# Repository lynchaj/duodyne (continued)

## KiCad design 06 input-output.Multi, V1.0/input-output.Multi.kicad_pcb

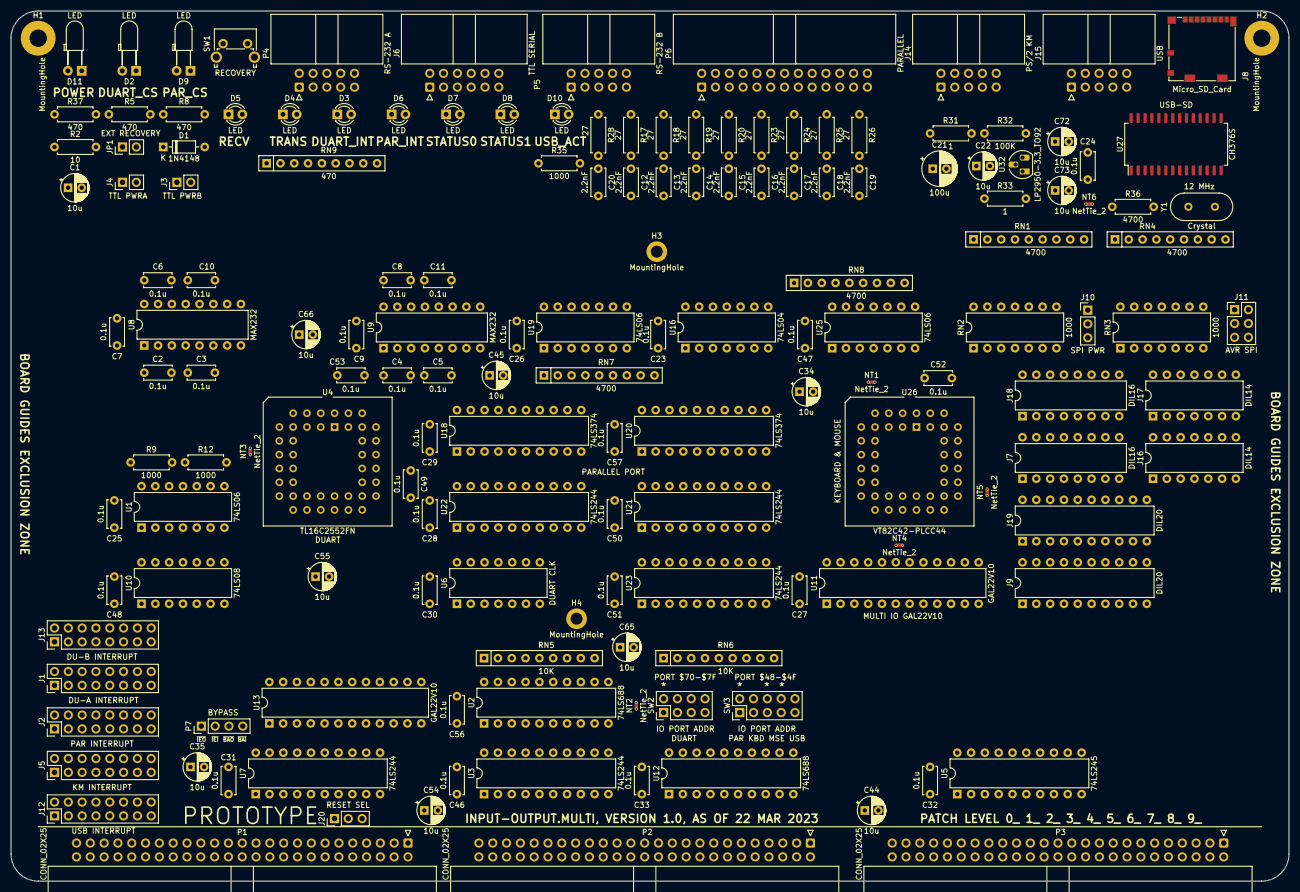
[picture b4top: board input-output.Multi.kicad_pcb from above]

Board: 2 copper layers, 235.0 x 160.0 mm, 159 parts (0 on the bottom side), 229 nets, no tracks yet.

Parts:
C1, C22, C34, C35, C44, C45, C54, C55, C65, C66, C72, C73: 10u; CP_Radial_D5.0mm_P2.50mm
C2, C3, C4, C5, C6, C7, C8, C9, C10, C11, C23, C24, C25, C26, C27, C28, C29, C30, C31, C32, C33, C46, C47, C48, C49, C50, C51, C52, C53, C56, C57: 0.1u; C_Disc_D5.0mm_W2.5mm_P5.00mm
C12, C13, C14, C15, C16, C17, C18, C19, C20: 2.2nF; C_Disc_D5.0mm_W2.5mm_P5.00mm
C21: 100u; CP_Radial_D6.3mm_P2.50mm
D1: 1N4148; D_DO-35_SOD27_P7.62mm_Horizontal
D2, D9, D11: LED; LED_D3.0mm_Horizontal_O3.81mm_Z2.0mm
D3, D4, D5, D6, D7, D8, D10: LED; LED_D3.0mm
H1, H2: MountingHole; MountingHole_3.2mm_M3_Pad
H3, H4: MountingHole; MountingHole_2.2mm_M2_DIN965_Pad
J1: DU-A INTERRUPT; PinHeader_2x08_P2.54mm_Vertical
J2: PAR INTERRUPT; PinHeader_2x08_P2.54mm_Vertical
J3: TTL PWRB; PinHeader_1x02_P2.54mm_Vertical
J4: TTL PWRA; PinHeader_1x02_P2.54mm_Vertical
J5: KM INTERRUPT; PinHeader_2x08_P2.54mm_Vertical
J6: TTL SERIAL; IDC-Header_2x06_P2.54mm_Horizontal
J7, J18: DIL16; DIP-16_W7.62mm
J8: Micro_SD_Card; microSD_HC_Molex_104031-0811
J9, J19: DIL20; DIP-20_W7.62mm
J10: SPI PWR; PinHeader_1x03_P2.54mm_Vertical
J11: AVR SPI; PinHeader_2x03_P2.54mm_Vertical
J12: USB INTERRUPT; PinHeader_2x08_P2.54mm_Vertical
J13: DU-B INTERRUPT; PinHeader_2x08_P2.54mm_Vertical
J14: PS/2 KM; IDC-Header_2x05_P2.54mm_Horizontal
J15: USB; IDC-Header_2x05_P2.54mm_Horizontal
J16, J17: DIL14; DIP-14_W7.62mm
J20: RESET SEL; PinHeader_1x03_P2.54mm_Vertical
JP1: EXT RECOVERY; PinHeader_1x02_P2.54mm_Vertical
NT1, NT2, NT3, NT4, NT5, NT6: NetTie_2; NetTie-2_THT_Pad0.3mm
P1, P2, P3: CONN_02X25; IDC-Header_2x25_P2.54mm_Horizontal
P4: RS-232 A; IDC-Header_2x05_P2.54mm_Horizontal
P5: RS-232 B; IDC-Header_2x05_P2.54mm_Horizontal
P6: PARALLEL; IDC-Header_2x13_P2.54mm_Horizontal
P7: BYPASS; PinHeader_1x04_P2.54mm_Vertical
R2: 10; R_Axial_DIN0207_L6.3mm_D2.5mm_P7.62mm_Horizontal
R5, R8, R37: 470; R_Axial_DIN0207_L6.3mm_D2.5mm_P7.62mm_Horizontal
R9, R12, R35: 1000; R_Axial_DIN0207_L6.3mm_D2.5mm_P7.62mm_Horizontal
R17, R18, R19, R20, R23, R24, R25, R26, R28: 27; R_Axial_DIN0207_L6.3mm_D2.5mm_P7.62mm_Horizontal
R31, R33: 1; R_Axial_DIN0207_L6.3mm_D2.5mm_P7.62mm_Horizontal
R32: 100K; R_Axial_DIN0207_L6.3mm_D2.5mm_P7.62mm_Horizontal
R36: 4700; R_Axial_DIN0207_L6.3mm_D2.5mm_P7.62mm_Horizontal
RN1, RN4, RN7, RN8: 4700; R_Array_SIP9
RN2, RN3: 1000; DIP-14_W7.62mm
RN5, RN6: 10K; R_Array_SIP9
RN9: 470; R_Array_SIP9
SW1: RECOVERY; SW_Tactile_SPST_Angled_PTS645Vx58-2LFS
SW2: IO PORT ADDR; PinHeader_2x04_P2.54mm_Vertical
SW3: IO PORT ADDR; PinHeader_2x05_P2.54mm_Vertical
U1, U19, U25: 74LS06; DIP-14_W7.62mm
U2, U12: 74LS688; DIP-20_W7.62mm
U3, U7, U21, U22, U23: 74LS244; DIP-20_W7.62mm
U4: TL16C2552FN; PLCC-44_THT-Socket
U5: 74LS245; DIP-20_W7.62mm
U6: DUART CLK; DIP-14_W7.62mm
U8, U9: MAX232; DIP-16_W7.62mm
U10: 74LS08; DIP-14_W7.62mm
U11, U13: GAL22V10; DIP-24_W7.62mm
U16: 74LS04; DIP-14_W7.62mm
U18, U20: 74LS374; DIP-20_W7.62mm
U26: VT82C42-PLCC44; PLCC-44_THT-Socket
U27: CH376S; SOIC-28W_7.5x18.7mm_P1.27mm
U32: LP2950-3.3_TO92; TO-92_HandSolder
Y1: Crystal; Crystal_HC49-4H_Vertical

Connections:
470A: D2.2 (A), RN9.2 (R1)
470B: D9.2 (A), RN9.3 (R2)
470C: D5.2 (A), RN9.4 (R3)
470D: D4.2 (A), RN9.5 (R4)
470E: D3.2 (A), RN9.6 (R5)
470F: D6.2 (A), RN9.7 (R6)
470G: D7.2 (A), RN9.8 (R7)
470H: D8.2 (A), RN9.9 (R8)
+12V: P2.19, P2.20
-12V: P2.37, P2.38
/DUART/GND_UART: NT3.1, U4.12 (GND)
/DUART/INTA: R12.1, U1.5, U4.34 (INTA)
/DUART/INTB: R9.1, U1.3, U4.17 (INTB)
/DUART/RXA: P4.3, U8.8 (R2IN)
/DUART/RXB: P5.3, U9.8 (R2IN)
/DUART/TTL_RXA: J6.7, U4.39 (RXA), U8.9 (R2OUT), U10.4
/DUART/TTL_RXB: J6.8, U4.25 (RXB), U9.9 (R2OUT), U10.5
/DUART/TTL_TXA: J6.9, U4.38 (TXA), U8.10 (T2IN), U10.1
/DUART/TTL_TXB: J6.10, U4.26 (TXB), U9.10 (T2IN), U10.2
/DUART/TXA: P4.5, U8.7 (T2OUT)
/DUART/TXB: P5.5, U9.7 (T2OUT)
/DUART/~CTSA: P4.6, U8.13 (R1IN)
/DUART/~CTSB: P5.6, U9.13 (R1IN)
/DUART/~DTRA: P4.7, R5.1
/DUART/~DTRB: P5.7, R8.1
/DUART/~INTA: J1.1, J1.3, J1.5, J1.7, J1.9, J1.11, J1.13, J1.15, U1.6, U10.9
/DUART/~INTB: J13.1, J13.3, J13.5, J13.7, J13.9, J13.11, J13.13, J13.15, U1.4, U10.10
/DUART/~RTSA: P4.4, U8.14 (T1OUT)
/DUART/~RTSB: P5.4, U9.14 (T1OUT)
/DUART/~TTL_CTSA: J6.11, U4.40 (~CTSA), U8.12 (R1OUT)
/DUART/~TTL_CTSB: J6.12, U4.28 (~CTSB), U9.12 (R1OUT)
/DUART/~TTL_RIA: C1.1, D1.2 (A), R2.2, RN5.9 (R8), U4.43 (~RIA)
/DUART/~TTL_RTSA: J6.3, U4.36 (~RTSA), U8.11 (T1IN)
/DUART/~TTL_RTSB: J6.4, U4.23 (~RTSB), U9.11 (T1IN)
/USB-SD/RST: R36.1, RN3.9 (R6.2), U27.2 (RSTI)
/USB-SD/SDCK: J8.5 (CLK), J11.3, U27.26 (SD_CK)
/USB-SD/SDCS: J8.2 (DAT3/CD), J11.5, RN4.6 (R5), U27.23 (SD_CS)
/USB-SD/SDDI: J8.3 (CMD), J11.1, U27.25 (SD_DO)
/USB-SD/SDDO: J8.7 (DAT0), J11.4, RN4.7 (R6), U27.7 (SD_DI)
/USB-SD/UD+: J15.5, J15.6, U27.10 (UD+)
/USB-SD/UD-: J15.3, J15.4, U27.11 (UD-)
/USB-SD/VBUS: C21.1, J15.1, J15.2, R31.2
/USB-SD/VDD2: C24.1, NT6.1, U27.28 (VCC)
/USB-SD/VDD3: C22.1, C23.1, J8.4 (VDD), R33.2
/USB-SD/~INT-USB: RN4.8 (R7), U16.1, U27.1 (~INT)
/kbdmse/KBDCLK: J14.1, RN8.3 (R2), U25.4, U26.2 (T0)
/kbdmse/KBDDAT: J14.9, RN8.5 (R4), U25.2, U26.30 (P10)
/kbdmse/MSECLK: J14.2, RN8.2 (R1), U25.8, U26.43 (T1)
/kbdmse/MSEDAT: J14.10, RN8.4 (R3), U25.6, U26.31 (P11)
/kbdmse/PROG: RN8.6 (R5), U26.28 (PROG)
/kbdmse/~INT_KM: J5.1, J5.3, J5.5, J5.7, J5.9, J5.11, J5.13, J5.15, U25.12
/parallel/BUSY: RN7.6 (R5), U19.2, U21.17 (I3b)
/parallel/ERROR: P6.4, U21.8 (I3a)
/parallel/P-RESET: P6.6, RN7.4 (R3), U19.10, U23.6 (I2a)
/parallel/PAPEROUT: P6.23, U21.13 (I1b)
/parallel/PD0: C12.1, P6.3, R17.1, U22.2 (I0a)
/parallel/PD1: C13.1, P6.5, R18.1, U22.4 (I1a)
/parallel/PD2: C14.1, P6.7, R19.1, U22.6 (I2a)
/parallel/PD3: C15.1, P6.9, R20.1, U22.8 (I3a)
/parallel/PD4: C16.1, P6.11, R23.1, U22.11 (I0b)
/parallel/PD5: C17.1, P6.13, R24.1, U22.13 (I1b)
/parallel/PD6: C18.1, P6.15, R25.1, U22.15 (I2b)
/parallel/PD7: C19.1, P6.17, R26.1, U22.17 (I3b)
/parallel/SELECT: P6.25, U21.11 (I0b)
/parallel/STATUS0: P6.26, U1.11, U20.16 (O6), U23.15 (I2b)
/parallel/STATUS1: U1.13, U20.19 (O7), U23.17 (I3b)
/parallel/~BUSY: P6.21, U19.1
/parallel/~INT_PAR: J2.1, J2.3, J2.5, J2.7, J2.9, J2.11, J2.13, J2.15, U19.12
/parallel/~LINEFEED: P6.2, RN7.3 (R2), U16.11, U19.8
/parallel/~PDENBL: U18.1 (OE), U20.15 (O5), U23.13 (I1b)
/parallel/~SEL: P6.8, RN7.5 (R4), U16.13, U19.4
/parallel/~STROBE: C20.1, P6.1, R28.1, RN7.2 (R1), U16.9
A0: P2.35, U3.2 (I0a)
A1: P2.33, U3.4 (I1a)
A2: P2.31, U3.6 (I2a)
A3: P2.29, U3.8 (I3a)
A4: P2.27, U3.11 (I0b)
A5: P2.25, U3.13 (I1b)
A6: P2.23, U3.15 (I2b)
A7: P2.21, U3.17 (I3b)
ACK: P6.19, U11.10 (I9), U21.15 (I2b)
CLK_DUART: U4.11 (XTAL1), U6.8, U6.11, U26.4 (X2)
D0: P3.33, U5.2 (A0)
D1: P3.31, U5.3 (A1)
D2: P3.29, U5.4 (A2)
D3: P3.27, U5.5 (A3)
D4: P3.25, U5.6 (A4)
D5: P3.23, U5.7 (A5)
D6: P3.21, U5.8 (A6)
D7: P3.19, U5.9 (A7)
GND: C1.2, C7.2, C9.2, C10.2, C11.2, C12.2, C13.2, C14.2, C15.2, C16.2, C17.2, C18.2, C19.2, C20.2, C21.2, C22.2, C23.2, C24.2, C25.2, C26.2, C27.2, C28.2, C29.2, C30.2, C31.2, C32.2, C33.2, C34.2, C35.2, C44.2, C45.2, C46.2, C47.2, C48.2, C49.2, C50.2, C51.2, C52.2, C53.2, C54.2, C55.2, C56.2, C57.2, C65.2, C66.2, C72.2, C73.2, D11.1 (K), H1.1, H2.1, J6.1, J6.2, J8.6 (VSS), J8.9 (SHIELD), J11.6, J14.5, J14.6, J15.7, J15.8, JP1.1 (A), NT2.1, NT3.2, NT4.1, P1.49, P1.50, P2.49, P2.50, P3.49, P3.50, P4.9, P5.9, P6.10, P6.12, P6.14, P6.16, P6.18, P6.20, P6.22, P6.24, R9.2, R12.2, R36.2, SW1.1, U1.7 (GND), U2.10 (GND), U3.10 (GND), U4.22 (GND), U5.10 (GND), U6.4, U6.7, U7.10 (GND), U8.15 (GND), U9.15 (GND), U10.7 (GND), U11.12 (GND), U12.10 (GND), U13.12 (GND), U16.7 (GND), U18.10 (GND), U19.7 (GND), U20.10 (GND), U21.10 (GND), U22.10 (GND), U23.10 (GND), U25.7 (GND), U27.12 (GND), U32.2 (GND)
INT_KM: U11.14 (O9), U25.13
INT_PAR: U1.9, U11.15 (O8), U19.13
unnamed: C2.1, U8.1 (C1+)
unnamed: C2.2, U8.3 (C1-)
unnamed: C3.1, U8.4 (C2+)
unnamed: C3.2, U8.5 (C2-)
unnamed: C4.1, U9.1 (C1+)
unnamed: C4.2, U9.3 (C1-)
unnamed: C5.1, U9.4 (C2+)
unnamed: C5.2, U9.5 (C2-)
unnamed: C6.2, U8.2 (VS+)
unnamed: C8.2, U9.2 (VS+)
unnamed: C10.1, U8.6 (VS-)
unnamed: C11.1, U9.6 (VS-)
unnamed: D2.1 (K), U7.16 (O1a)
unnamed: D3.1 (K), U10.8
unnamed: D4.1 (K), U10.3
unnamed: D5.1 (K), U10.6
unnamed: D6.1 (K), U1.8
unnamed: D7.1 (K), U1.10
unnamed: D8.1 (K), U1.12
unnamed: D9.1 (K), U10.11
unnamed: D10.1 (K), R35.1
unnamed: D11.2 (A), R37.1
unnamed: J3.2, J6.6
unnamed: J4.2, J6.5
unnamed: J8.1 (DAT2), J8.8 (DAT1), R32.2
unnamed: J10.2, J11.2
unnamed: J12.1, J12.3, J12.5, J12.7, J12.9, J12.11, J12.13, J12.15, U25.10
unnamed: J20.2, U7.2 (I0a)
unnamed: JP1.2 (B), R2.1, SW1.2
unnamed: R17.2, U18.2 (O0)
unnamed: R18.2, U18.5 (O1)
unnamed: R19.2, U18.6 (O2)
unnamed: R20.2, U18.9 (O3)
unnamed: R23.2, U18.12 (O4)
unnamed: R24.2, U18.15 (O5)
unnamed: R25.2, U18.16 (O6)
unnamed: R26.2, U18.19 (O7)
unnamed: R28.2, U19.6
unnamed: R35.2, U27.24 (~ACT)
unnamed: RN1.2 (R1), RN3.14 (R1.2), U27.22 (D7)
unnamed: RN1.3 (R2), RN2.14 (R1.2), U27.21 (D6)
unnamed: RN1.4 (R3), RN2.13 (R2.2), U27.20 (D5)
unnamed: RN1.5 (R4), RN2.12 (R3.2), U27.19 (D4)
unnamed: RN1.6 (R5), RN2.11 (R4.2), U27.18 (D3)
unnamed: RN1.7 (R6), RN2.10 (R5.2), U27.17 (D2)
unnamed: RN1.8 (R7), RN2.9 (R6.2), U27.16 (D1)
unnamed: RN1.9 (R8), RN2.8 (R7.2), U27.15 (D0)
unnamed: RN3.10 (R5.2), RN4.5 (R4), U27.27 (~PCS)
unnamed: RN3.11 (R4.2), RN4.4 (R3), U27.3 (~WR)
unnamed: RN3.12 (R3.2), RN4.3 (R2), U27.4 (~RD)
unnamed: RN3.13 (R2.2), RN4.2 (R1), U27.8 (A0)
unnamed: RN5.2 (R1), SW2.1, U2.18 (R7)
unnamed: RN5.3 (R2), SW2.3, U2.16 (R6)
unnamed: RN5.4 (R3), SW2.5, U2.14 (R5)
unnamed: RN5.5 (R4), SW2.7, U2.12 (R4)
unnamed: RN5.6 (R5), U2.3 (R0), U2.4 (P1), U2.5 (R1), U2.6 (P2), U2.7 (R2), U2.8 (P3), U2.9 (R3)
unnamed: RN6.2 (R1), SW3.1, U12.18 (R7)
unnamed: RN6.3 (R2), SW3.3, U12.16 (R6)
unnamed: RN6.4 (R3), SW3.5, U12.14 (R5)
unnamed: RN6.5 (R4), SW3.7, U12.12 (R4)
unnamed: RN6.6 (R5), SW3.9, U12.9 (R3)
unnamed: RN6.7 (R6), U12.3 (R0), U12.4 (P1), U12.5 (R1), U12.6 (P2), U12.7 (R2)
unnamed: U16.2, U25.11
unnamed: U16.5, U20.6 (O2)
unnamed: U16.6, U19.11
unnamed: U16.8, U23.2 (I0a)
unnamed: U16.10, U23.4 (I1a)
unnamed: U16.12, U23.8 (I3a)
unnamed: U19.3, U20.9 (O3)
unnamed: U19.5, U20.2 (O0)
unnamed: U19.9, U20.5 (O1)
unnamed: U25.1, U26.42 (P27/DAK)
unnamed: U25.3, U26.41 (P26/DRQ)
unnamed: U25.5, U26.26 (P22)
unnamed: U25.9, U26.27 (P23)
unnamed: U27.13 (XI), Y1.1
unnamed: U27.14 (XO), Y1.2
ONE: NT1.2, U26.6 (SS)
P24-OB: U11.11 (I10), U26.39 (P24/OB)
P25-BF: U11.13 (I11), U26.40 (P25/BF)
PARINT: U11.9 (I8), U20.12 (O4), U23.11 (I0b)
VCC: C6.1, C7.1, C8.1, C9.1, C25.1, C26.1, C27.1, C28.1, C29.1, C30.1, C31.1, C32.1, C33.1, C34.1, C35.1, C44.1, C45.1, C46.1, C47.1, C48.1, C49.1, C50.1, C51.1, C52.1, C53.1, C54.1, C55.1, C56.1, C57.1, C65.1, C66.1, C72.1, D1.1 (K), J3.1, J4.1, J10.3, J14.3, J14.4, NT1.1, NT5.2, P1.1, P1.2, P2.1, P2.2, P3.1, P3.2, R5.2, R8.2, R31.1, R37.2, RN5.1 (common), RN6.1 (common), RN7.1 (common), RN8.1 (common), RN9.1 (common), U1.14 (VCC), U2.20 (VCC), U3.20 (VCC), U4.33 (VCC), U4.44 (VCC), U5.20 (VCC), U6.1, U6.14, U7.20 (VCC), U8.16 (VCC), U9.16 (VCC), U10.14 (VCC), U11.24 (VCC), U12.20 (VCC), U13.24 (VCC), U16.14 (VCC), U18.20 (VCC), U19.14 (VCC), U20.20 (VCC), U21.20 (VCC), U22.20 (VCC), U23.20 (VCC), U25.14 (VCC), U26.44 (VCC), U32.3 (VI)
VDD: NT5.1, U26.29 (VDD)
VDD1: C73.1, D10.2 (A), J10.1, NT6.2, R32.1, R33.1, RN1.1 (common), RN4.1 (common), U27.9 (V3), U32.1 (VO)
VSS: NT4.2, U26.22 (VSS)
ZERO: NT2.2, SW2.2, SW2.4, SW2.6, SW2.8, SW3.2, SW3.4, SW3.6, SW3.8, SW3.10, U3.1 (OEa), U3.19 (OEb), U7.1 (OEa), U7.19 (OEb), U20.1 (OE), U26.3 (X1), U26.8 (EA), U27.5 (TXD)
bA0: RN3.2 (R2.1), U3.18 (O0a), U4.10 (A0), U11.4 (I3), U26.10 (A0)
bA1: U3.16 (O1a), U4.14 (A1), U11.5 (I4)
bA2: U3.14 (O2a), U4.15 (A2), U11.6 (I5)
bA3: U3.12 (O3a), U4.16 (CHSEL), U12.8 (P3)
bA4: U2.11 (P4), U3.9 (O0b), U12.11 (P4)
bA5: U2.13 (P5), U3.7 (O1b), U12.13 (P5)
bA6: U2.15 (P6), U3.5 (O2b), U12.15 (P6)
bA7: U2.17 (P7), U3.3 (O3b), U12.17 (P7)
bD0: RN2.7 (R7.1), U4.2 (D0), U5.18 (B0), U18.3 (D0), U20.3 (D0), U21.18 (O0a), U22.18 (O0a), U23.18 (O0a), U26.14 (D0)
bD1: RN2.6 (R6.1), U4.3 (D1), U5.17 (B1), U18.4 (D1), U20.4 (D1), U21.16 (O1a), U22.16 (O1a), U23.16 (O1a), U26.15 (D1)
bD2: RN2.5 (R5.1), U4.4 (D2), U5.16 (B2), U18.7 (D2), U20.7 (D2), U21.14 (O2a), U22.14 (O2a), U23.14 (O2a), U26.16 (D2)
bD3: RN2.4 (R4.1), U4.5 (D3), U5.15 (B3), U18.8 (D3), U20.8 (D3), U21.12 (O3a), U22.12 (O3a), U23.12 (O3a), U26.17 (D3)
bD4: RN2.3 (R3.1), U4.6 (D4), U5.14 (B4), U18.13 (D4), U20.13 (D4), U21.9 (O0b), U22.9 (O0b), U23.9 (O0b), U26.18 (D4)
bD5: RN2.2 (R2.1), U4.7 (D5), U5.13 (B5), U18.14 (D5), U20.14 (D5), U21.7 (O1b), U22.7 (O1b), U23.7 (O1b), U26.19 (D5)
bD6: RN2.1 (R1.1), U4.8 (D6), U5.12 (B6), U18.17 (D6), U20.17 (D6), U21.5 (O2b), U22.5 (O2b), U23.5 (O2b), U26.20 (D6)
bD7: RN3.1 (R1.1), U4.9 (D7), U5.11 (B7), U18.18 (D7), U20.18 (D7), U21.3 (O3b), U22.3 (O3b), U23.3 (O3b), U26.21 (D7)
bRESET: RN3.6 (R6.1), U4.21 (RESET), U16.4
~BAI: P1.40, P7.4
~BAO: P1.42, P7.3
~BUS_EN: U5.19 (CE), U11.16 (O7)
~CS_DUART: U2.19 (P=R), U4.18 (~CS), U7.4 (I1a), U11.8 (I7)
~CS_KM: U11.18 (O5), U26.7 (CS)
~CS_PAR: U10.12, U10.13, U11.7 (I6), U12.19 (P=R)
~CS_US: RN3.5 (R5.1), U11.17 (O6)
~EIRQ0: J1.2, J2.2, J5.2, J12.2, J13.2, P1.45
~EIRQ1: J1.4, J2.4, J5.4, J12.4, J13.4, P1.43
~EIRQ2: J1.6, J2.6, J5.6, J12.6, J13.6, P1.41
~EIRQ3: J1.8, J2.8, J5.8, J12.8, J13.8, P1.39
~EIRQ4: J1.10, J2.10, J5.10, J12.10, J13.10, P1.37
~EIRQ5: J1.12, J2.12, J5.12, J12.12, J13.12, P1.35
~EIRQ6: J1.14, J2.14, J5.14, J12.14, J13.14, P1.33
~EIRQ7: J1.16, J2.16, J5.16, J12.16, J13.16, P1.31
~IEI: P1.44, P7.2
~IEO: P1.46, P7.1
~IORQ: P1.7, U7.11 (I0b)
~M1: P1.11, U7.13 (I1b)
~PARIN0: U11.23 (O0), U22.1 (OEa), U22.19 (OEb)
~PARIN1: U11.22 (O1), U21.1 (OEa), U21.2 (I0a), U21.4 (I1a), U21.6 (I2a), U21.19 (OEb)
~PARIN2: U11.21 (O2), U23.1 (OEa), U23.19 (OEb)
~PAROUT0: U11.20 (O3), U18.11 (Cp)
~PAROUT2: U11.19 (O4), U20.11 (Cp)
~RD: P1.3, U5.1 (A->B), U7.17 (I3b)
~RES_IN: J20.1, P1.20
~RES_OUT: J20.3, P1.21
~WR: P1.5, U7.15 (I2b)
~bIORQ: U2.1 (G), U7.9 (O0b), U12.1 (G)
~bM1: U2.2 (P0), U7.7 (O1b), U12.2 (P0)
~bRD: RN3.3 (R3.1), U4.24 (~IOR), U7.3 (O3b), U11.2 (I1), U26.9 (RD)
~bRESET: U7.18 (O0a), U16.3, U26.5 (RESET)
~bWR: RN3.4 (R4.1), U4.20 (~IOW), U7.5 (O2b), U11.3 (I2), U26.11 (WR)
